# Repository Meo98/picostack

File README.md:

<h1 align="center">PicoStack</h1>

<p align="center">
  <b>A stackable, contract-driven module system for the Raspberry Pi Pico.</b><br>
  Open hardware, generated by code, verified by tests that are proven to fail.
</p>

<p align="center">

</p>

---

**One board plus a Pico is a working device.** PicoStack v2 abolishes the
separate base board that v1 needed: every 75 × 65 mm module now carries its
own 6–30 V supply (reverse-polarity protection, TVS, a K7805-1000R3
regulator, Schottky-OR into VSYS) and a pair of Pico-native 1×20 socket rows
(17.78 mm apart, the Pico's own pinout) — the Pico plugs straight into the
top of the stack and all 40 pins run down through it. Stack several fed
boards and they coexist; one is enough to power the whole chain. Every
module also breaks out its 18 spare Pico GPIOs plus 3V3/GND as labelled
solder pads on the board edge.

Power, I²C, emergency-stop and flashing signals run through the stack on
the same contract pinout v1 defined — v2 changed the connector geometry,
not a single pin's role — and any module can be flashed **through the
stack**, selected by a hardware token chain, without touching a cable.

The unusual part: **these boards are not drawn, they are built.** Schematics,
placement, routing, ground stitching and the manufacturing checks all come
from Python that runs headless against KiCad. The stack's mechanical and
electrical rules live in a single machine-readable file — the *contract*
(see the [design spec](docs/superpowers/specs/2026-09-07-picostack-v2-design.md)
for the full v2 rationale) — and every board is measured against it before
it may exist.

## Why you might care

- **You want motorized / sensor / whatever hats for the Pico** that stack
  instead of sprawling across a desk. Design one module and it composes
  with all the others.
- **You want to see a fully generative KiCad workflow** — schematic
  generators, placement specs, headless autorouting (freerouting 2.3),
  copper-pour healing, DRC gates — all reproducible from the command line.
- **You like tests that can actually fail.** Every check in this repository
  ships with a proof that it turns red when the thing it guards is broken.
  ERC and DRC caught *none* of the 14+ real bugs found during development —
  including a fail-unsafe emergency-stop gate (an intact loop blocked the
  motor, a broken wire released it) and a reverse-polarity FET wired so
  that reverse voltage crowbarred instead of being blocked. The custom
  gates caught all of them; that story is documented in the code.

## The stack at a glance

| Piece | What it is | State |
|---|---|---|
| **Contract** (`tools/stack_spec.py`) | Connector positions, pin roles, per-module supply rules, edge-pad positions, landing-point copper rules, mating rules — the single source of truth for anyone building a module | stable, v2 |
| **Motor module** (`hardware/kicad/motor/`) | DRV8876 H-bridge, STM32C011 co-processor, opto-isolated dual-channel e-stop loop, own 6–30 V supply cell | 75 × 65 mm, routed, DRC-clean |
| **Dimmer family** (`hardware/kicad/dimmer{1,3,4}/`) | 1/3/4-channel low-side LED dimmers from one parametric description, own supply cell each | 75 × 65 mm, routed, DRC-clean |
| **Base board** (`hardware/kicad/sockel/`) | v1's Pico socket + 24 V input + 5 V rail board | **v1-only, archived** — see [release v0.1.0](https://github.com/Meo98/picostack/releases/tag/v0.1.0); not part of v2, not updated to the v2 contract |
| **Toolchain** (`tools/`) | Schematic generators, board builder, autorouter driver, ground healer, contract probes | working, evolving |

## How a board gets built

```text
tools/sch/<board>.py      →  KiCad schematic (generated, ERC-clean)
tools/pcb/spec_<board>.py →  placement + pre-routes + stitching, no KiCad needed
tools/pcb/build.py        →  fresh .kicad_pcb from netlist + spec
tools/pcb/autoroute.py    →  freerouting 2.3 headless, DSN repaired on the fly
tools/pcb/masseheiler.py  →  finds isolated copper islands, heals them with vias
tools/pcb/steckerprobe.py →  measures the finished board against the contract
```

Every stage is a plain Python file you can read, run and extend. The
[website](https://meo98.github.io/picostack/) walks through the architecture in
detail.

## Building a module of your own

The contract is deliberately small. A module must:

1. use the 75 × 65 mm outline and M3 hole pattern from `stack_spec.py`,
2. place the two Pico-native socket rows and the two connector pairs at the
   contract positions (the helpers compute them for you — never type the
   coordinates),
3. give the board its own 6–30 V supply cell (reverse-polarity protection,
   TVS, Schottky-OR into VSYS) and bring every unused Pico GPIO out as a
   labelled edge pad,
4. keep the landing-point areas free of exposed copper, so a stack that is
   assembled rotated cannot short anything,
5. pass `tests/` and the contract probes against the built board.

Start by copying `tools/pcb/spec_motor.py` and
`tools/sch/motormodul.py`, then read
[CONTRIBUTING.md](CONTRIBUTING.md) — it describes the workflow, the
red-proof testing rule, and how to propose a new module.

**Module ideas we would love to see:** sensor hats, LED drivers, stepper
drivers, CAN/RS-485 bridges, audio, battery management — anything that
speaks the contract. Firmware in any language that runs on a Pico or the
module MCUs (C, MicroPython, Rust, …) is equally welcome.

## Repository layout

```text
hardware/kicad/     KiCad projects (generated .kicad_sch + built .kicad_pcb)
tools/stack_spec.py the contract
tools/sch/          schematic generators
tools/pcb/          board builder, router driver, probes, healer
tests/              plain-python test suites (no pytest needed)
docs/               project website (GitHub Pages)
```

## Building the boards yourself

You need KiCad 10, Python 3, and Java ≥ 25 for the bundled
freerouting 2.3 flow. Then:

```bash
python3 tests/run_all.py                 # every suite, no board tools needed
python3 tools/sch/motormodul.py          # regenerate a schematic
tools/pcb/kipy tools/pcb/build.py spec_motor \
  hardware/kicad/motor/Motormodul.kicad_pcb \
  hardware/kicad/motor/Motormodul.kicad_sch   # rebuild a board
```

(`kipy` is a small launcher that runs a script inside KiCad's Python.
See CONTRIBUTING for the full toolchain walkthrough.)

## Getting boards made

Gerbers, JLC-format BOM/CPL and pick-and-place files for all four v2 boards
live under `hardware/fertigung/{motor,dimmer1,dimmer3,dimmer4}/`, and ship as
ZIPs with every [release](https://github.com/Meo98/picostack/releases).
[`hardware/fertigung/ORDERING.md`](hardware/fertigung/ORDERING.md) walks
through ordering an assembled board at JLCPCB, including the traps that
already cost real money in v1 (a diode package mix-up, a rotation-preview
miss, a type-code encoding gotcha).

## License

- **Hardware** (everything under `hardware/`): [CERN-OHL-S-2.0](hardware/LICENSE) —
  strongly reciprocal: if you ship a derived board, you publish your changes.
- **Code** (tools, generators, firmware): [GPL-3.0-or-later](LICENSE).
- **Documentation**: CC-BY-SA 4.0.

## Project language

The public face of this project is English. The code comments are currently
German — they carry the full engineering rationale of every decision and are
being translated over time. New contributions should be in English.

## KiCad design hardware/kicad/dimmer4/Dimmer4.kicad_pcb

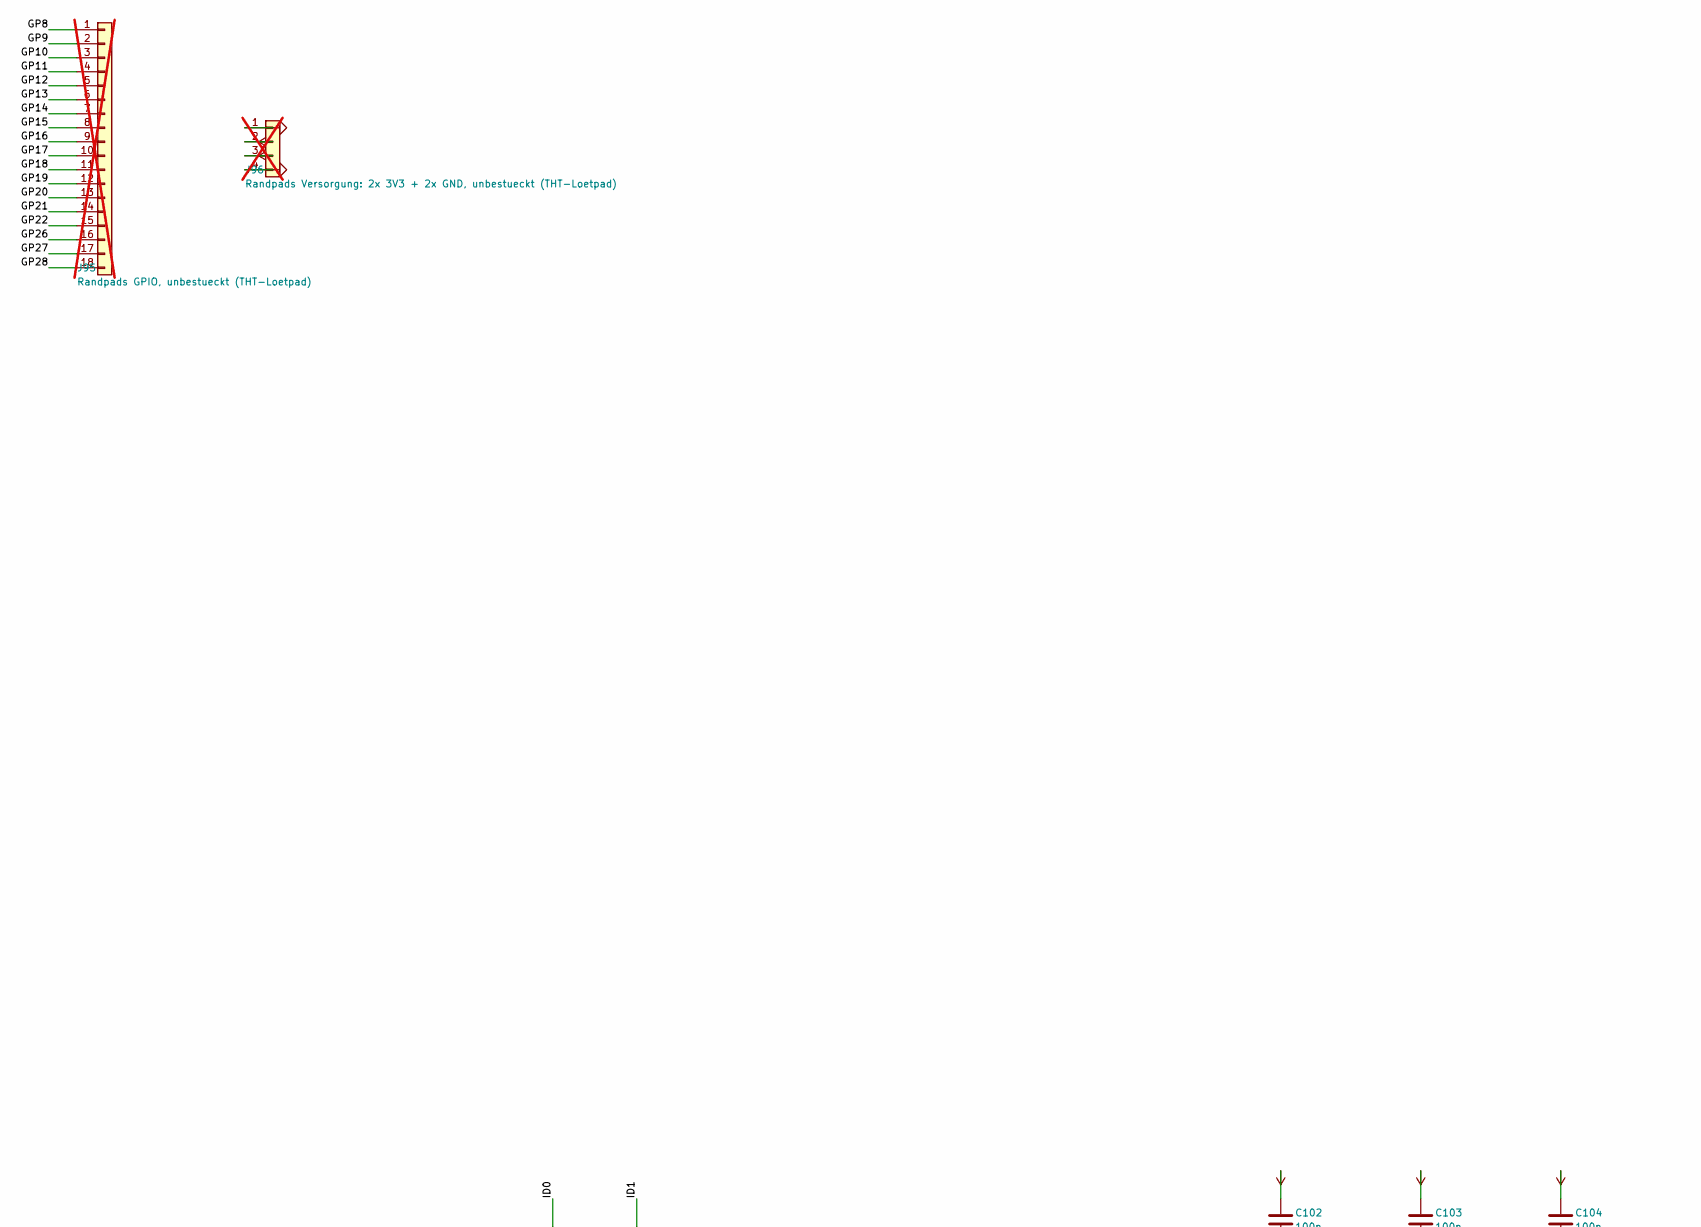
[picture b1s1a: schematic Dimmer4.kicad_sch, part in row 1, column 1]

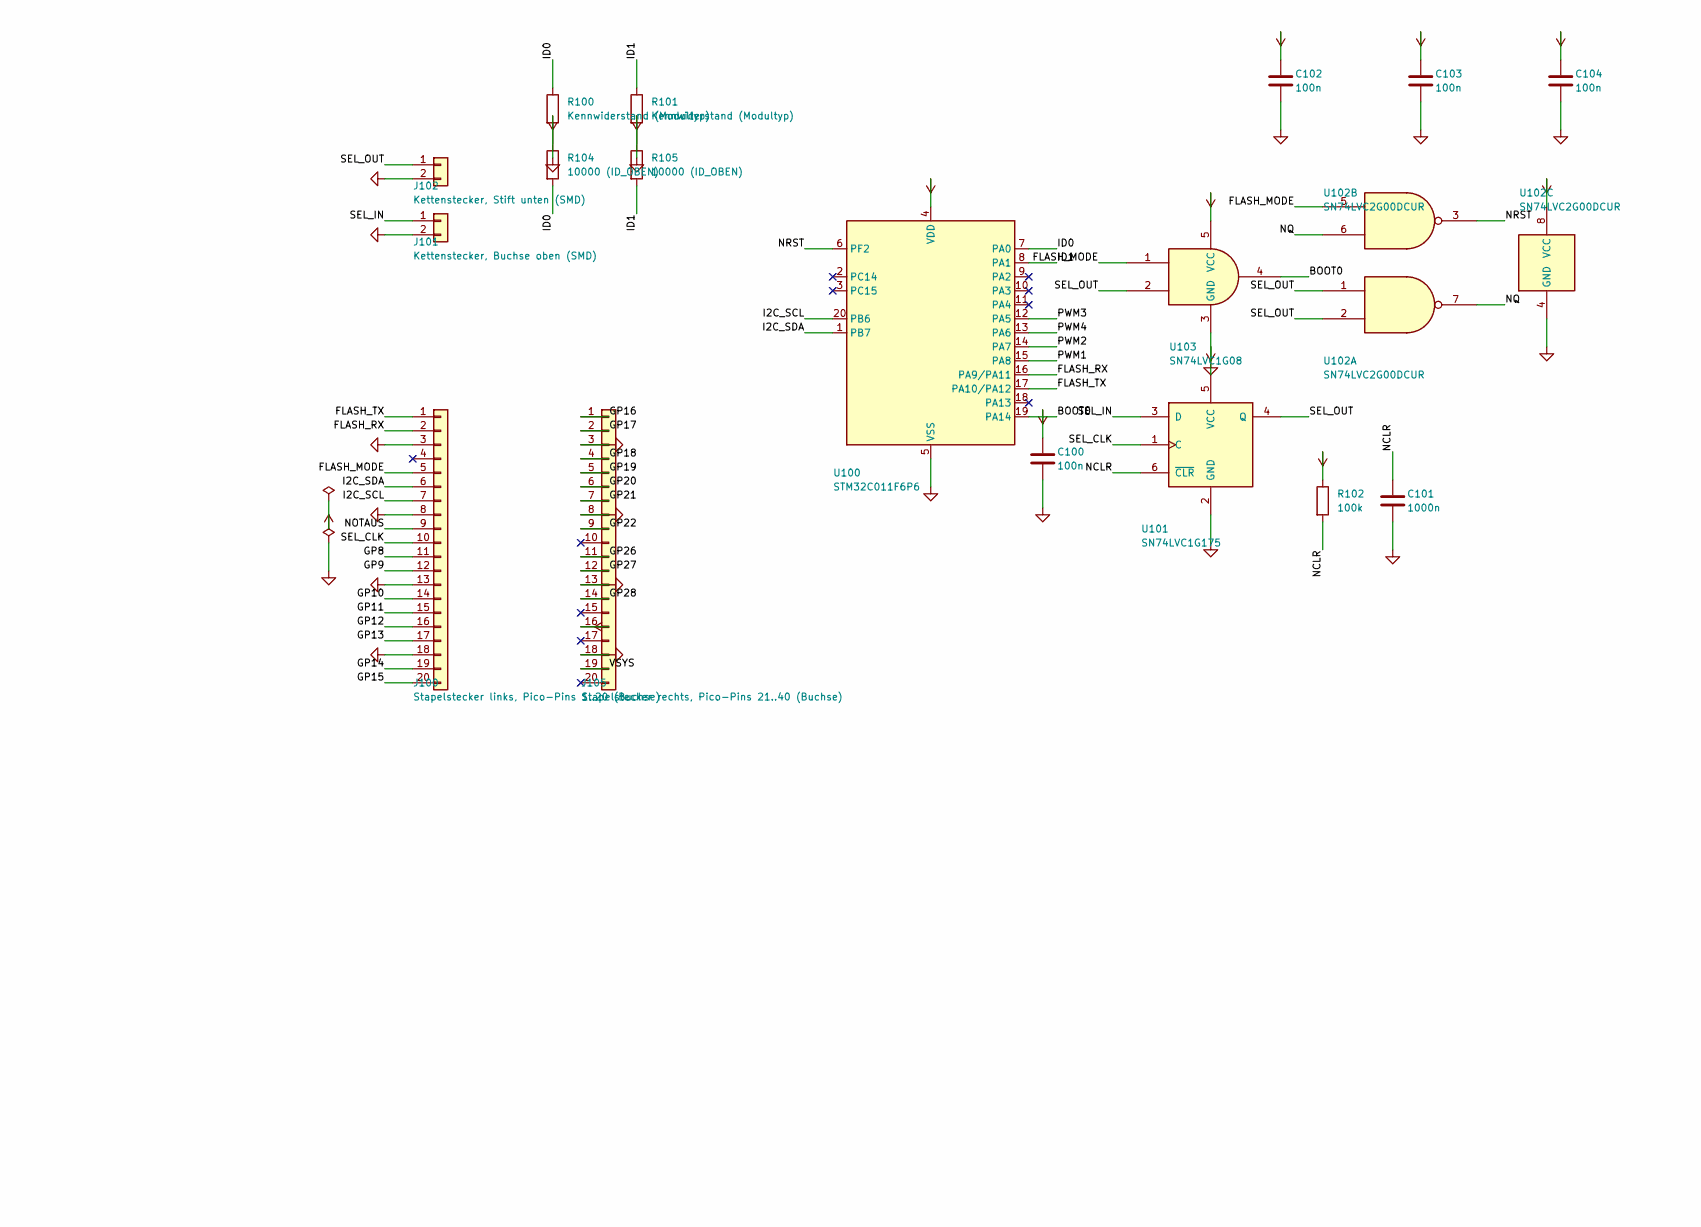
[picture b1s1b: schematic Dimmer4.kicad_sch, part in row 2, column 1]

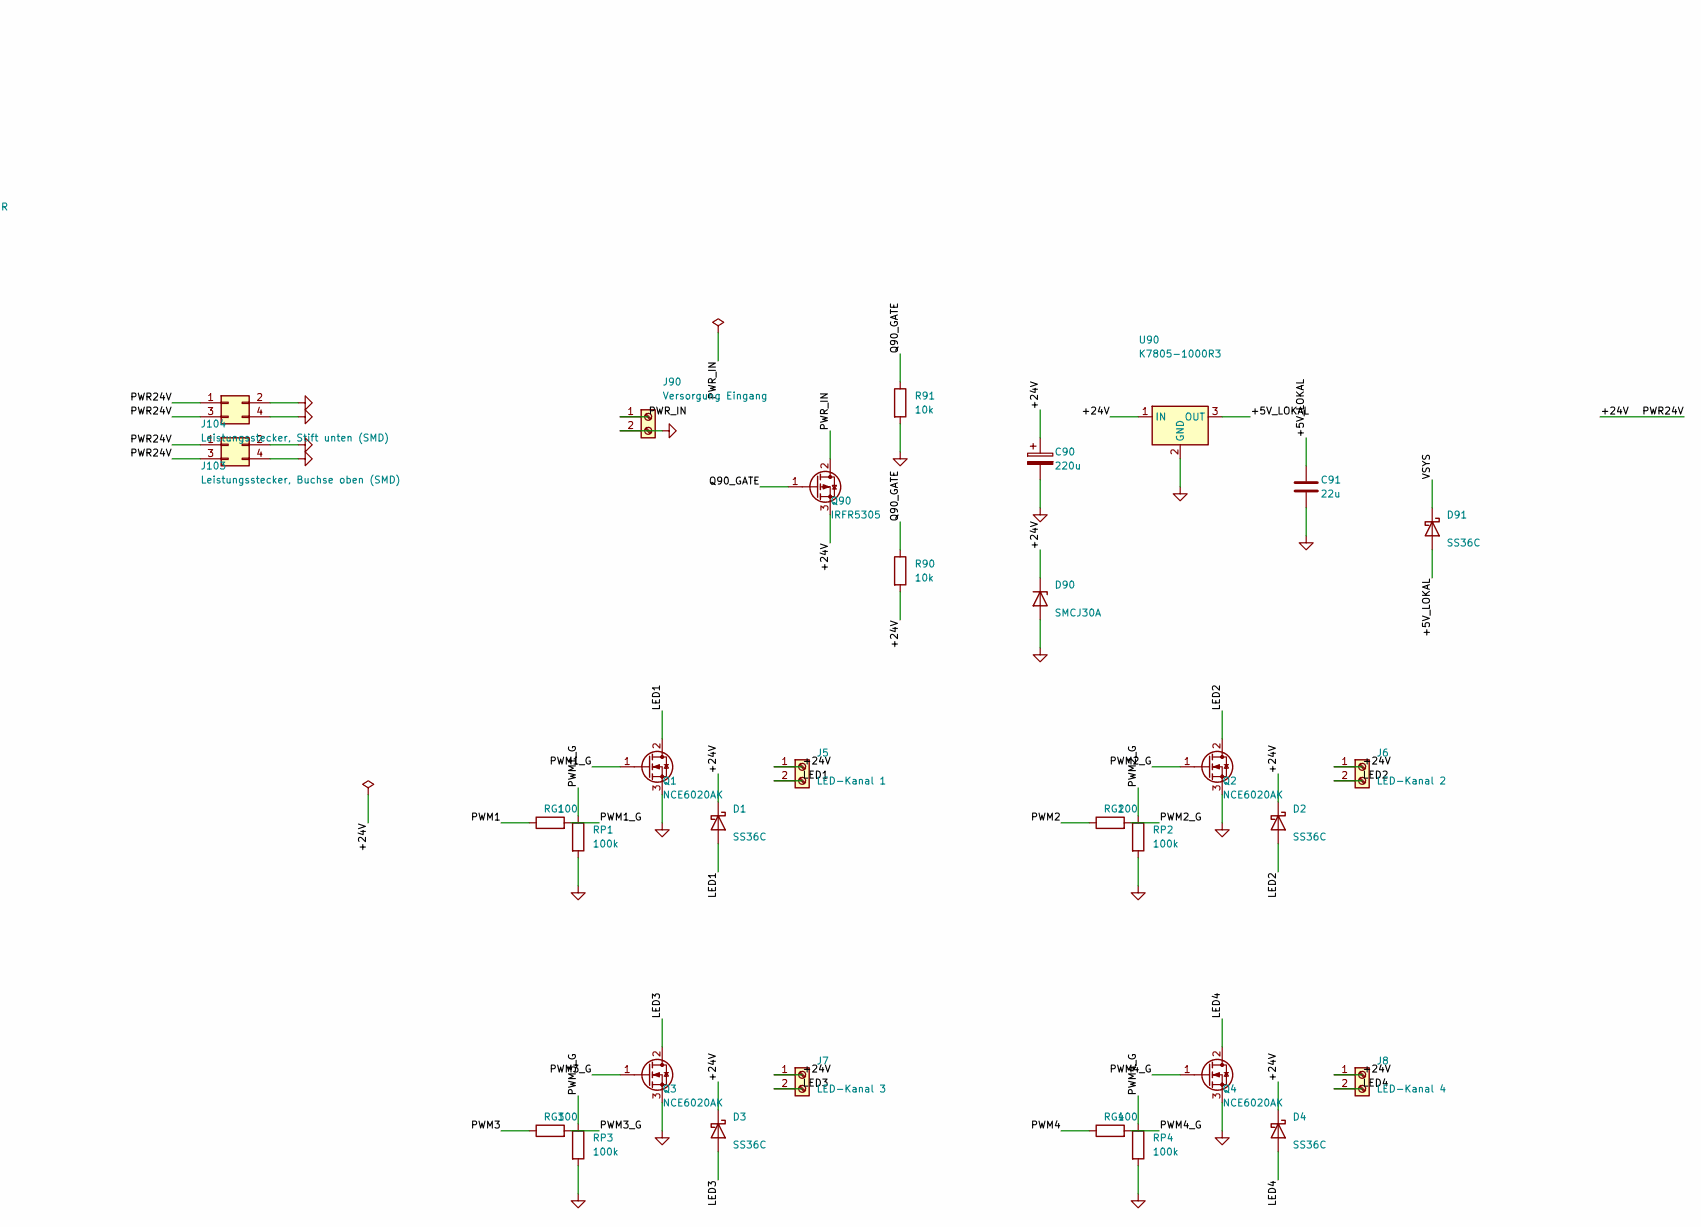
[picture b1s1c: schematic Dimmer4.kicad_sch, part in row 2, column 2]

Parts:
C90: 220u; CP_Radial_D8.0mm_P3.50mm
C91: 22u; C_0805_2012Metric_Pad1.18x1.45mm_HandSolder
C100: 100n; C_0805_2012Metric_Pad1.18x1.45mm_HandSolder
C101: 1000n; C_0805_2012Metric_Pad1.18x1.45mm_HandSolder
C102, C103, C104: 100n; C_0805_2012Metric_Pad1.18x1.45mm_HandSolder; LCSC C49678
D1, D2, D3, D4, D91: SS36C; D_SMC
D90: SMCJ30A; D_SMC
J5: LED-Kanal 1; TerminalBlock_Phoenix_PT-1,5-2-3.5-H_1x02_P3.50mm_Horizontal
J6: LED-Kanal 2; TerminalBlock_Phoenix_PT-1,5-2-3.5-H_1x02_P3.50mm_Horizontal
J7: LED-Kanal 3; TerminalBlock_Phoenix_PT-1,5-2-3.5-H_1x02_P3.50mm_Horizontal
J8: LED-Kanal 4; TerminalBlock_Phoenix_PT-1,5-2-3.5-H_1x02_P3.50mm_Horizontal
J90: Versorgung Eingang; TerminalBlock_Phoenix_PT-1,5-2-3.5-H_1x02_P3.50mm_Horizontal
J95: Randpads GPIO, unbestueckt (THT-Loetpad); Randpad_Reihe_1x18; not fitted
J96: Randpads Versorgung: 2x 3V3 + 2x GND, unbestueckt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; Randpad_Reihe_1x04; not fitted
J100: Stapelstecker links, Pico-Pins 1..20 (Buchse); PinSocket_1x20_P2.54mm_Vertical
J101: Kettenstecker, Buchse oben (SMD); PinSocket_1x02_P2.54mm_Vertical_SMD_Pin1Left
J102: Kettenstecker, Stift unten (SMD); PinHeader_1x02_P2.54mm_Vertical_SMD_Pin1Left
J103: Leistungsstecker, Buchse oben (SMD); PinSocket_2x02_P2.54mm_Vertical_SMD
J104: Leistungsstecker, Stift unten (SMD); PinHeader_2x02_P2.54mm_Vertical_SMD
J105: Stapelstecker rechts, Pico-Pins 21..40 (Buchse); PinSocket_1x20_P2.54mm_Vertical
Q1, Q2, Q3, Q4: NCE6020AK; TO-252-3_TabPin2
Q90: IRFR5305; TO-252-3_TabPin2
R90, R91: 10k; R_0805_2012Metric_Pad1.20x1.40mm_HandSolder
R100, R101: Kennwiderstand (Modultyp); R_0805_2012Metric_Pad1.20x1.40mm_HandSolder
R102: 100k; R_0805_2012Metric_Pad1.20x1.40mm_HandSolder
R104, R105: 10000 (ID_OBEN); R_0805_2012Metric_Pad1.20x1.40mm_HandSolder
RG1, RG2, RG3, RG4: 100; R_0805_2012Metric_Pad1.20x1.40mm_HandSolder
RP1, RP2, RP3, RP4: 100k; R_0805_2012Metric_Pad1.20x1.40mm_HandSolder
U90: K7805-1000R3; Converter_DCDC_RECOM_R-78B-2.0_THT
U100: STM32C011F6P6; TSSOP-20_4.4x6.5mm_P0.65mm
U101: SN74LVC1G175; SOT-363_SC-70-6
U102: SN74LVC2G00DCUR; VSSOP-8_2.3x2mm_P0.5mm
U103: SN74LVC1G08; SOT-353_SC-70-5

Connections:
/+5V_LOKAL: C91.1, D91.2 (A), U90.3 (OUT)
/+24V: C90.1, D1.1 (K), D2.1 (K), D3.1 (K), D4.1 (K), D90.1 (K), J5.1, J6.1, J7.1, J8.1, J103.1, J103.3, J104.1, J104.3, Q90.3 (S), R90.2, U90.1 (IN)
/BOOT0: U100.19 (PA14), U103.4
/FLASH_MODE: J100.5, U102.5, U103.1
/FLASH_RX: J100.2, U100.16 (PA9/PA11)
/FLASH_TX: J100.1, U100.17 (PA10/PA12)
/GP8: J95.1, J100.11
/GP9: J95.2, J100.12
/GP10: J95.3, J100.14
/GP11: J95.4, J100.15
/GP12: J95.5, J100.16
/GP13: J95.6, J100.17
/GP14: J95.7, J100.19
/GP15: J95.8, J100.20
/GP16: J95.9, J105.1
/GP17: J95.10, J105.2
/GP18: J95.11, J105.4
/GP19: J95.12, J105.5
/GP20: J95.13, J105.6
/GP21: J95.14, J105.7
/GP22: J95.15, J105.9
/GP26: J95.16, J105.11
/GP27: J95.17, J105.12
/GP28: J95.18, J105.14
/I2C_SCL: J100.7, U100.20 (PB6)
/I2C_SDA: J100.6, U100.1 (PB7)
/ID0: R100.1, R104.2, U100.7 (PA0)
/ID1: R101.1, R105.2, U100.8 (PA1)
/LED1: D1.2 (A), J5.2, Q1.2 (D)
/LED2: D2.2 (A), J6.2, Q2.2 (D)
/LED3: D3.2 (A), J7.2, Q3.2 (D)
/LED4: D4.2 (A), J8.2, Q4.2 (D)
/NCLR: C101.1, R102.2, U101.6 (~CLR)
/NOTAUS: J100.9
/NQ: U102.6, U102.7
/NRST: U100.6 (PF2), U102.3
/PWM1: RG1.1, U100.15 (PA8)
/PWM1_G: Q1.1 (G), RG1.2, RP1.1
/PWM2: RG2.1, U100.14 (PA7)
/PWM2_G: Q2.1 (G), RG2.2, RP2.1
/PWM3: RG3.1, U100.12 (PA5)
/PWM3_G: Q3.1 (G), RG3.2, RP3.1
/PWM4: RG4.1, U100.13 (PA6)
/PWM4_G: Q4.1 (G), RG4.2, RP4.1
/PWR_IN: J90.1, Q90.2 (D)
/Q90_GATE: Q90.1 (G), R90.1, R91.1
/SEL_CLK: J100.10, U101.1 (C)
/SEL_IN: J101.1, U101.3 (D)
/SEL_OUT: J102.1, U101.4 (Q), U102.1, U102.2, U103.2
/VSYS: D91.1 (K), J105.19

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
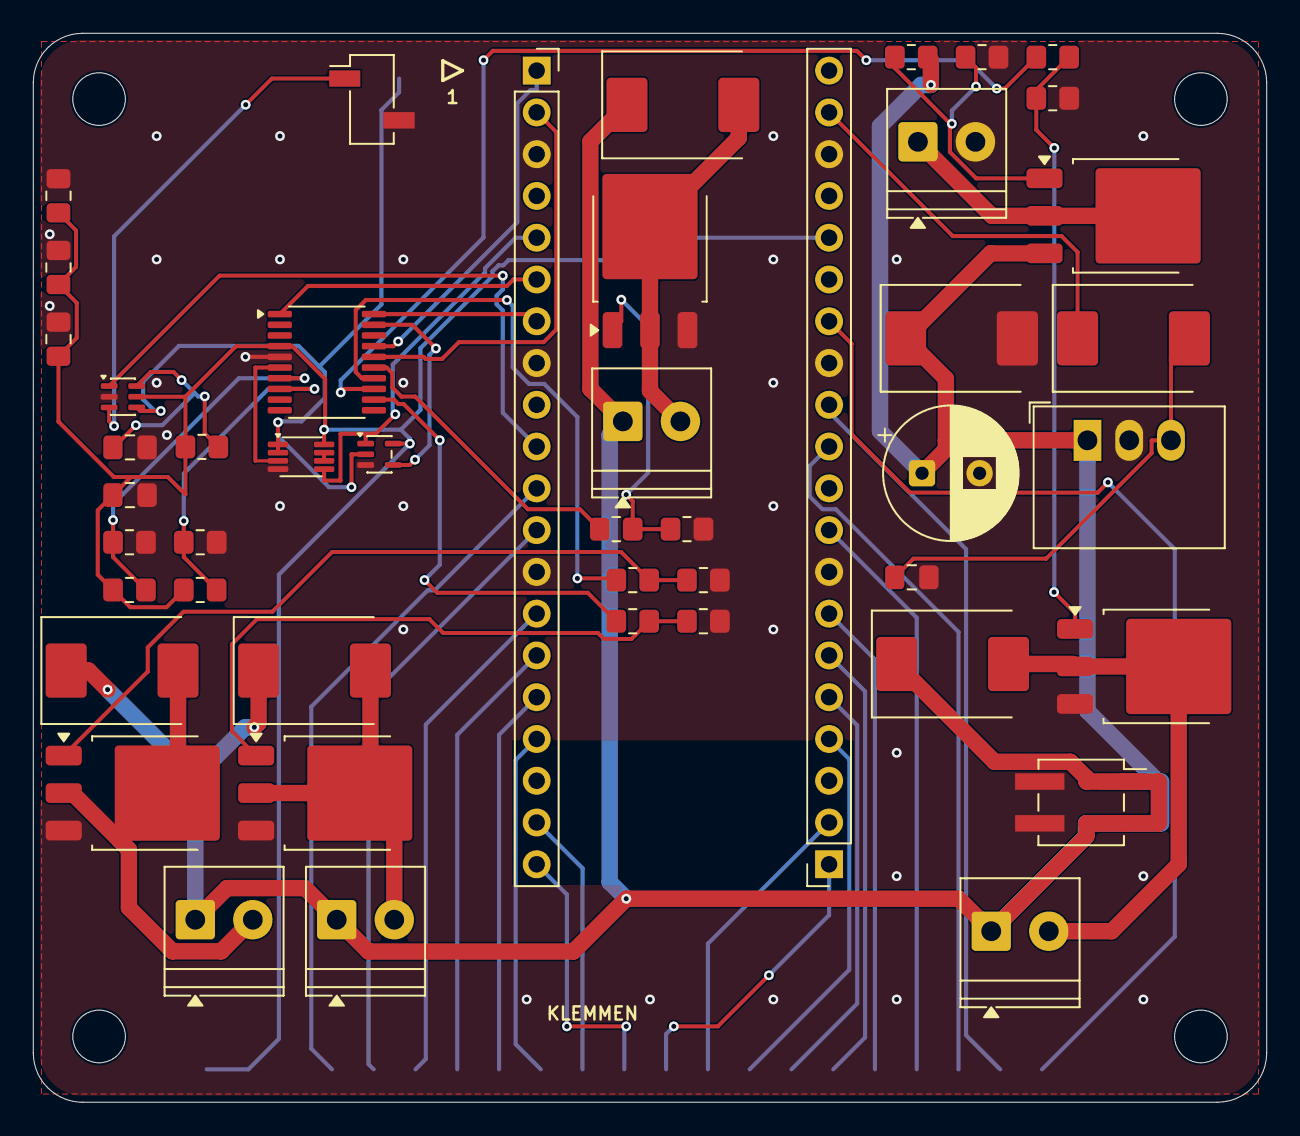
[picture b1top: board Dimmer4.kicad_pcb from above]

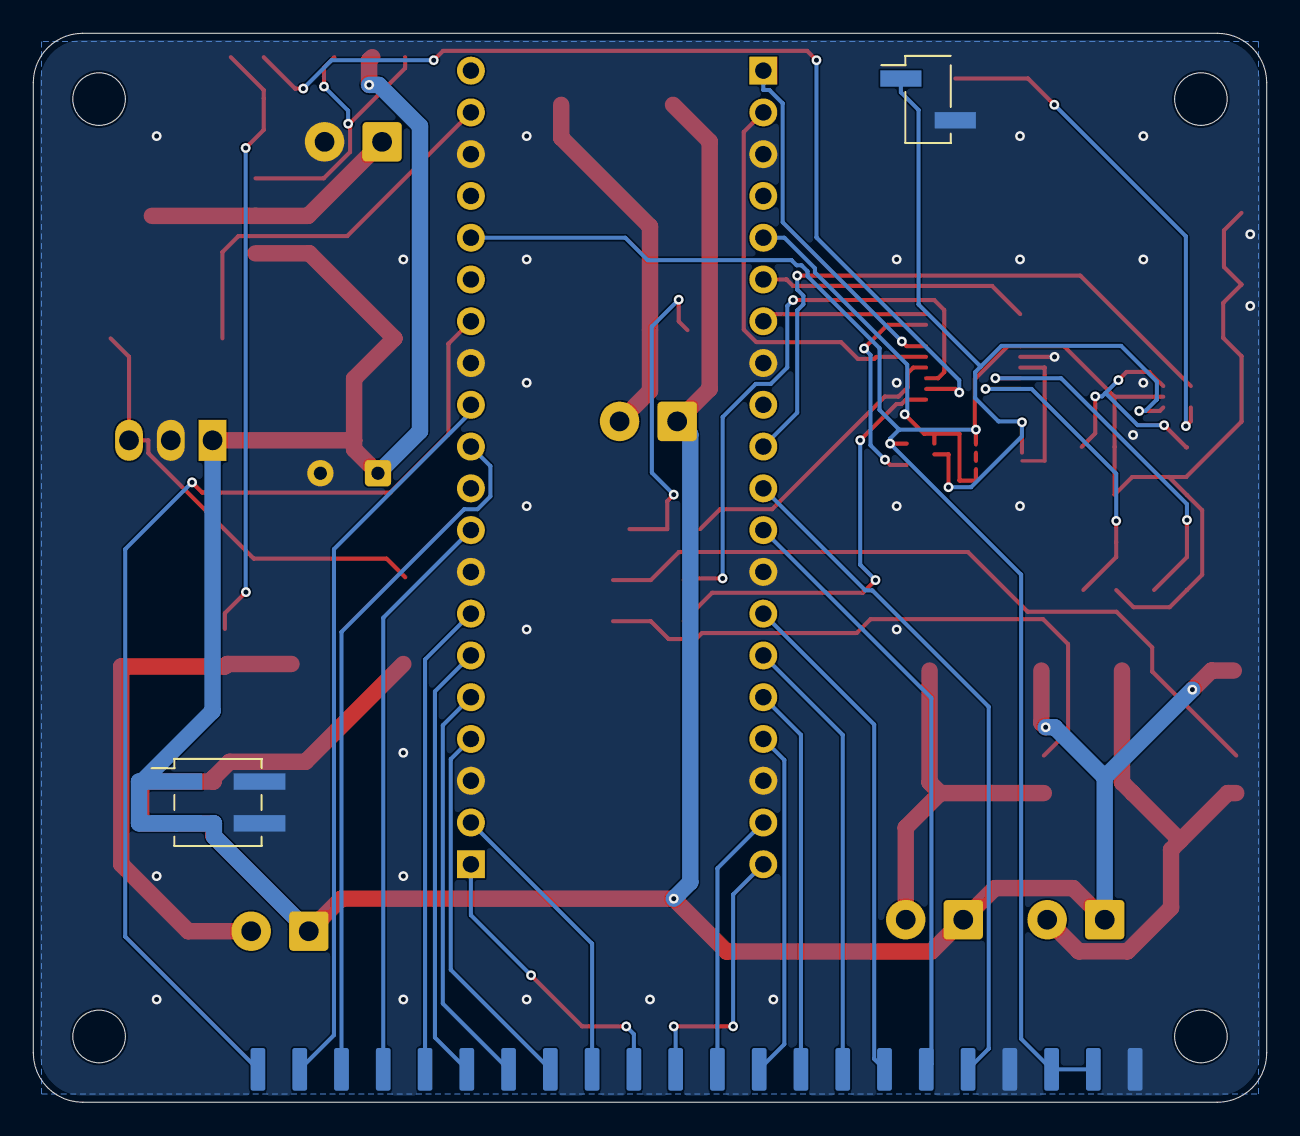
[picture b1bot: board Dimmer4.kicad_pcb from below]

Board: 2 copper layers, 75.0 x 65.0 mm, 55 parts (4 on the bottom side), 51 nets.

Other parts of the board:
H1, H2, H3, H4: M3

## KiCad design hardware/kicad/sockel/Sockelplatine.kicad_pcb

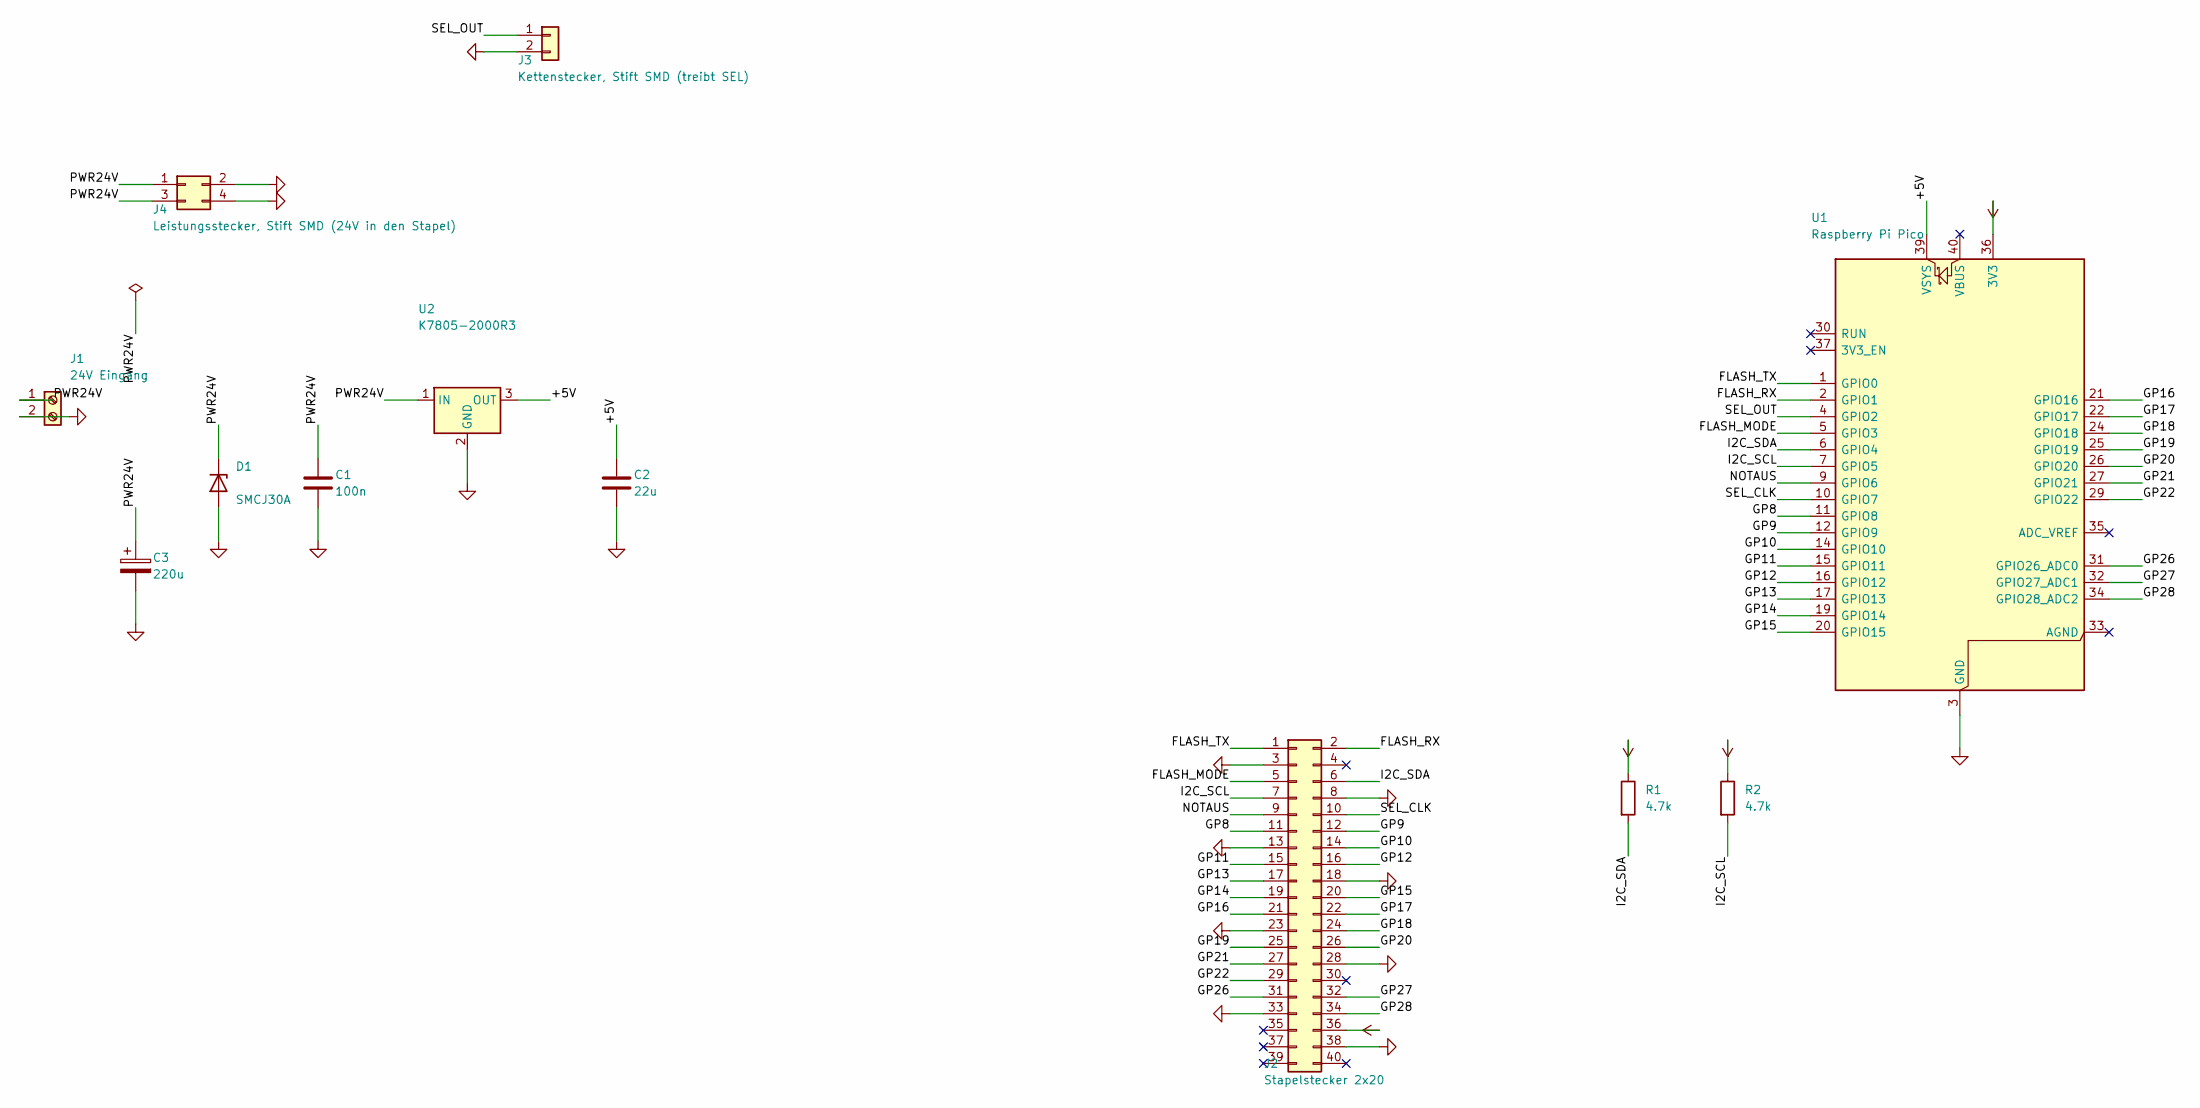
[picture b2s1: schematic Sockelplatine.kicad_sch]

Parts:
C1: 100n; C_0805_2012Metric_Pad1.18x1.45mm_HandSolder
C2: 22u; C_0805_2012Metric_Pad1.18x1.45mm_HandSolder
C3: 220u; CP_Radial_D8.0mm_P3.50mm
D1: SMCJ30A; D_SMC_Handsoldering
J1: 24V Eingang; TerminalBlock_Phoenix_MKDS-3-2-5.08_1x02_P5.08mm_Horizontal
J2: Stapelstecker 2x20; PinHeader_2x20_P2.54mm_Vertical
J3: Kettenstecker, Stift SMD (treibt SEL); PinHeader_1x02_P2.54mm_Vertical_SMD_Pin1Left
J4: Leistungsstecker, Stift SMD (24V in den Stapel); PinHeader_2x02_P2.54mm_Vertical_SMD
R1, R2: 4.7k; R_0805_2012Metric_Pad1.20x1.40mm_HandSolder
U1: Raspberry Pi Pico; RaspberryPi_Pico_Common_THT
U2: K7805-2000R3; Converter_DCDC_RECOM_R-78B-2.0_THT

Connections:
3V3: J2.36, R1.1, R2.1, U1.36 (3V3)
/+5V: C2.1, U1.39 (VSYS), U2.3 (OUT)
/FLASH_MODE: J2.5, U1.5 (GPIO3)
/FLASH_RX: J2.2, U1.2 (GPIO1)
/FLASH_TX: J2.1, U1.1 (GPIO0)
/GP8: J2.11, U1.11 (GPIO8)
/GP9: J2.12, U1.12 (GPIO9)
/GP10: J2.14, U1.14 (GPIO10)
/GP11: J2.15, U1.15 (GPIO11)
/GP12: J2.16, U1.16 (GPIO12)
/GP13: J2.17, U1.17 (GPIO13)
/GP14: J2.19, U1.19 (GPIO14)
/GP15: J2.20, U1.20 (GPIO15)
/GP16: J2.21, U1.21 (GPIO16)
/GP17: J2.22, U1.22 (GPIO17)
/GP18: J2.24, U1.24 (GPIO18)
/GP19: J2.25, U1.25 (GPIO19)
/GP20: J2.26, U1.26 (GPIO20)
/GP21: J2.27, U1.27 (GPIO21)
/GP22: J2.29, U1.29 (GPIO22)
/GP26: J2.31, U1.31 (GPIO26_ADC0)
/GP27: J2.32, U1.32 (GPIO27_ADC1)
/GP28: J2.34, U1.34 (GPIO28_ADC2)
/I2C_SCL: J2.7, R2.2, U1.7 (GPIO5)
/I2C_SDA: J2.6, R1.2, U1.6 (GPIO4)
/NOTAUS: J2.9, U1.9 (GPIO6)
/PWR24V: C1.1, C3.1, D1.1 (K), J1.1, J4.1, J4.3, U2.1 (IN)
/SEL_CLK: J2.10, U1.10 (GPIO7)
/SEL_OUT: J3.1, U1.4 (GPIO2)
GND: C1.2, C2.2, C3.2, D1.2 (A), J1.2, J2.3, J2.8, J2.13, J2.18, J2.23, J2.28, J2.33, J2.38, J3.2, J4.2, J4.4, U1.3 (GND), U1.8 (GND), U1.13 (GND), U1.18 (GND), U1.23 (GND), U1.28 (GND), U1.38 (GND), U2.2 (GND)

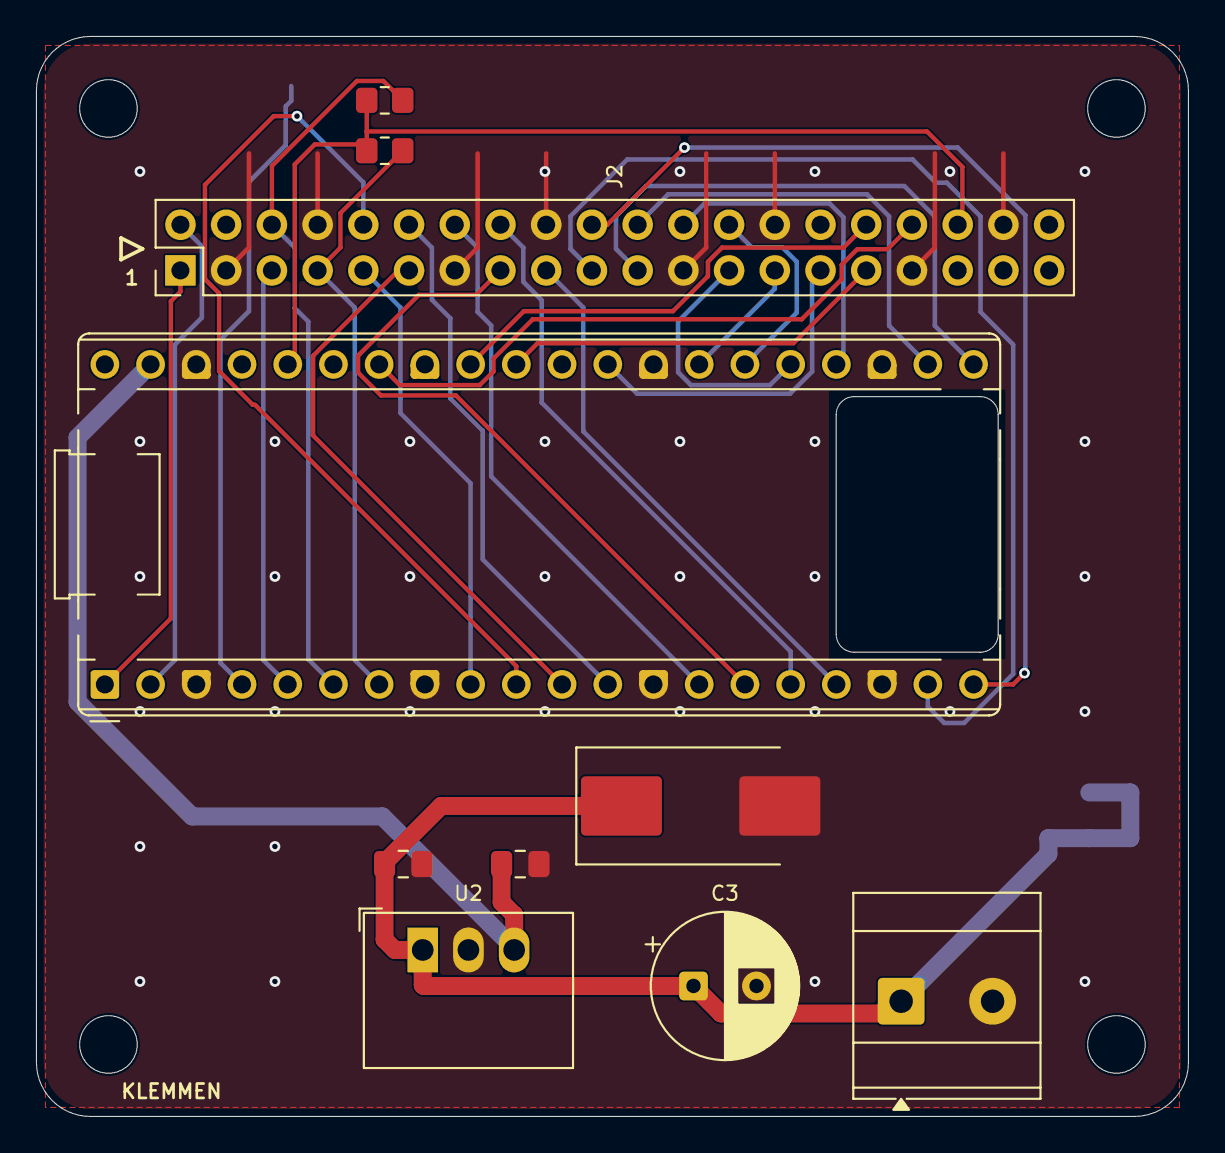
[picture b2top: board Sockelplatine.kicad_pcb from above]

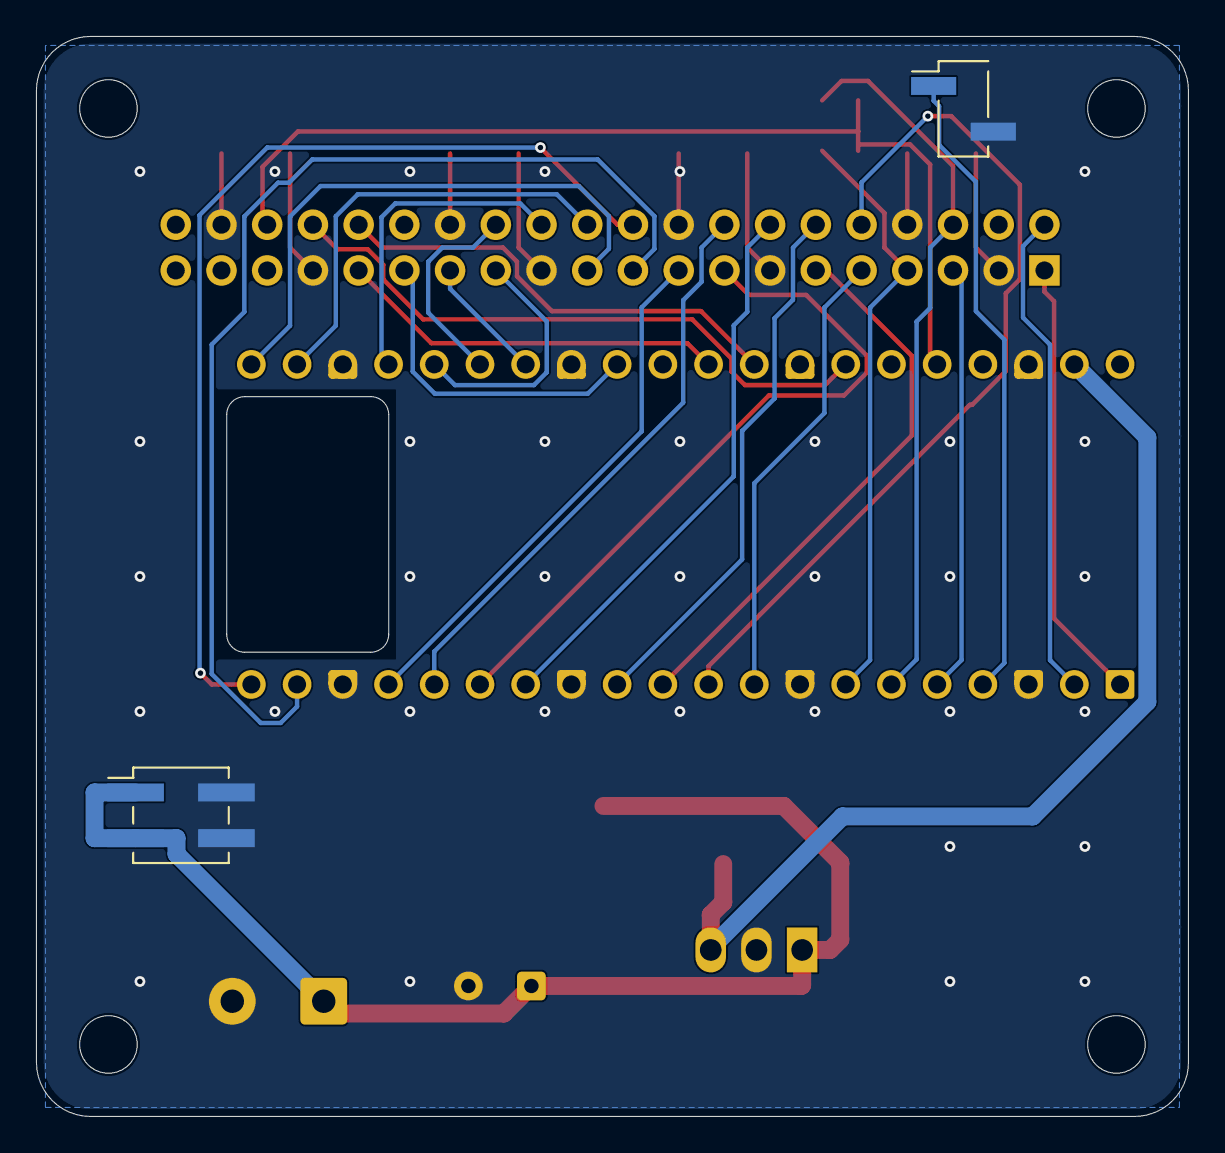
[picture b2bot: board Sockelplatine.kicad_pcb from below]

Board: 2 copper layers, 64.0 x 60.0 mm, 16 parts (2 on the bottom side), 30 nets.

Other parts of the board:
H1, H2, H3, H4: M3

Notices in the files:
README.md:
Code: GPLv3
